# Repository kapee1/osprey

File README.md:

## Remix of the most beautiful ergonomic monosplit in my opinion

### Why did i do it? 
I really likes how does look original Osprey, but it is very difficult to assemble it yourself. This remix allows you to build it much easier and it still can be wireless! However, the assembly is not the easiest due to the size of the diodes.
### What changed? 
It uses SuperMini as controller. I used original PCB as template, so outline barely changed to fit a MSK swtich near USB-port. I have to slightly change case usb-hole and add a switch cutout. But original plate still fits. 
### Thanks
Huge thanks to the [ebastler](https://github.com/ebastler), author of the [original project](https://github.com/ebastler/osprey) for the inspiration and for the great work he did on the original project and [aroum](https://github.com/aroum) for his kind help and advices. 
### BOM
To build firmware, simply clone this repo: https://github.com/kapee1/osprey-remix-zmk-config

| Part    |  Amount   |     |
| --- | --- | --- |
|   Osprey-remix PCB         |  1  |  1.2mm   |
|   Osprey Plate             |  1  |  1.2mm   |
|   Osprey-remix Bottom case |   1  |     |
|   Osprey-remix Top case    |   1  |     |
|   M2 x 8mm screws          |  9   |     |
|   Threaded M2 inserts      |  9   |     |
|   SuperMini or Nice!Nano   |  1   |     |
|   Kailh Choc Hotswap sockets    |  42   |     |
|   1N4148WS SOD-323 Diodes   |  42  |     |
|   MSK-12C01 Switch         |  1   |     |
|   502030 Battery           |  1   |     |
|   Round 8mm feets          |  7   |     |

## Photos

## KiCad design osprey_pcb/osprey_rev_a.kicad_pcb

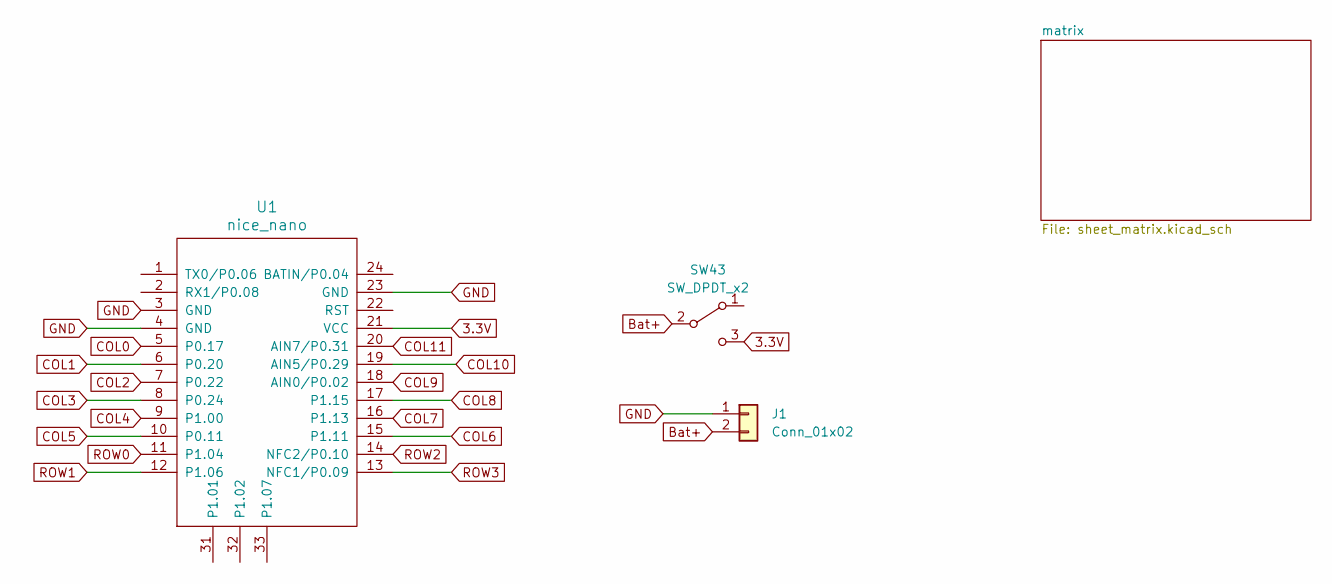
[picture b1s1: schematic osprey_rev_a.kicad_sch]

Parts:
J1: Conn_01x02; JST_ACH_BM02B-ACHSS-GAN-ETF_1x02-1MP_P1.20mm_Vertical
SW43: SW_DPDT_x2; MSK12C02
U1: nice_nano; NiceNano

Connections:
3.3V: SW43.3 (C), U1.21 (VCC), U1.26
Bat+: J1.2, SW43.2 (B); also elsewhere on the board
COL0: U1.5 (P0.17); also elsewhere on the board
COL1: U1.6 (P0.20); also elsewhere on the board
COL2: U1.7 (P0.22); also elsewhere on the board
COL3: U1.8 (P0.24); also elsewhere on the board
COL4: U1.9 (P1.00); also elsewhere on the board
COL5: U1.10 (P0.11); also elsewhere on the board
COL6: U1.15 (P1.11); also elsewhere on the board
COL7: U1.16 (P1.13); also elsewhere on the board
COL8: U1.17 (P1.15); also elsewhere on the board
COL9: U1.18 (AIN0/P0.02); also elsewhere on the board
COL10: U1.19 (AIN5/P0.29); also elsewhere on the board
COL11: U1.20 (AIN7/P0.31); also elsewhere on the board
GND: J1.1, U1.3 (GND), U1.4 (GND), U1.23 (GND), U1.25; also elsewhere on the board
ROW0: U1.11 (P1.04); also elsewhere on the board
ROW1: U1.12 (P1.06); also elsewhere on the board
ROW2: U1.14 (NFC2/P0.10); also elsewhere on the board
ROW3: U1.13 (NFC1/P0.09); also elsewhere on the board

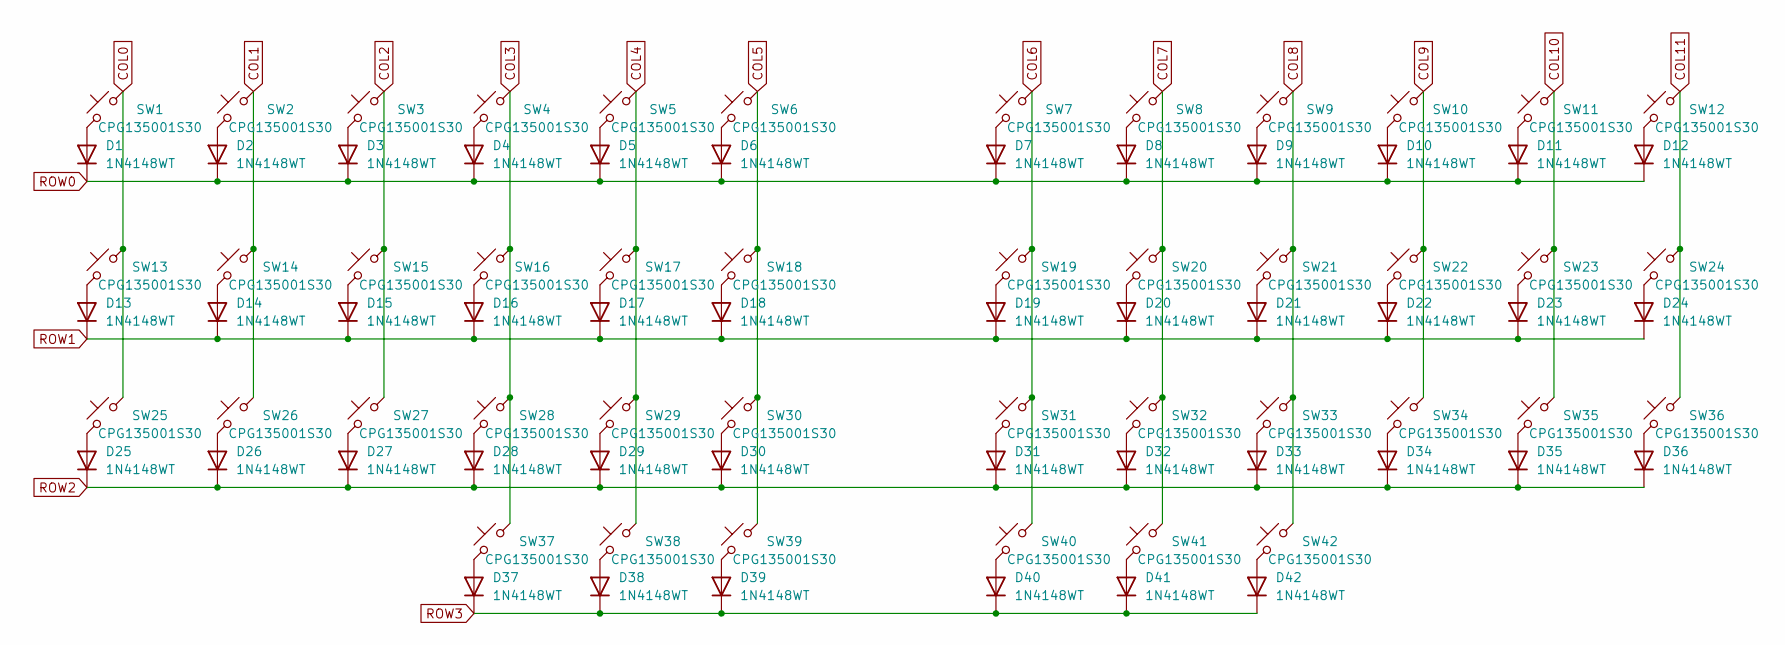
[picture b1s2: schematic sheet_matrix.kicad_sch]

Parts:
D1, D2, D3, D4, D5, D6, D7, D8, D9, D10, D11, D12, D13, D14, D15, D16, D17, D18, D19, D20, D21, D22, D23, D24, D25, D26, D27, D28, D29, D30, D31, D32, D33, D34, D35, D36, D37, D38, D39, D40, D41, D42: 1N4148WT; D_SOD-323_HandSoldering
SW1, SW2, SW3, SW4, SW5, SW6, SW7, SW8, SW9, SW10, SW11, SW12, SW13, SW14, SW15, SW16, SW17, SW18, SW19, SW20, SW21, SW22, SW23, SW24, SW25, SW26, SW27, SW28, SW29, SW30, SW31, SW32, SW33, SW34, SW35, SW36, SW37, SW38, SW41, SW42: CPG135001S30; SW_choc_HS_1u
SW39, SW40: CPG135001S30; SW_choc_HS_1.5u

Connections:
COL0: SW1.1, SW13.1, SW25.1; also elsewhere on the board
COL1: SW2.1, SW14.1, SW26.1; also elsewhere on the board
COL2: SW3.1, SW15.1, SW27.1; also elsewhere on the board
COL3: SW4.1, SW16.1, SW28.1, SW37.1; also elsewhere on the board
COL4: SW5.1, SW17.1, SW29.1, SW38.1; also elsewhere on the board
COL5: SW6.1, SW18.1, SW30.1, SW39.1; also elsewhere on the board
COL6: SW7.1, SW19.1, SW31.1, SW40.1; also elsewhere on the board
COL7: SW8.1, SW20.1, SW32.1, SW41.1; also elsewhere on the board
COL8: SW9.1, SW21.1, SW33.1, SW42.1; also elsewhere on the board
COL9: SW10.1, SW22.1, SW34.1; also elsewhere on the board
COL10: SW11.1, SW23.1, SW35.1; also elsewhere on the board
COL11: SW12.1, SW24.1, SW36.1; also elsewhere on the board
unnamed: D1.2 (A), SW1.2
unnamed: D2.2 (A), SW2.2
unnamed: D3.2 (A), SW3.2
unnamed: D4.2 (A), SW4.2
unnamed: D5.2 (A), SW5.2
unnamed: D6.2 (A), SW6.2
unnamed: D7.2 (A), SW7.2
unnamed: D8.2 (A), SW8.2
unnamed: D9.2 (A), SW9.2
unnamed: D10.2 (A), SW10.2
unnamed: D11.2 (A), SW11.2
unnamed: D12.2 (A), SW12.2
unnamed: D13.2 (A), SW13.2
unnamed: D14.2 (A), SW14.2
unnamed: D15.2 (A), SW15.2
unnamed: D16.2 (A), SW16.2
unnamed: D17.2 (A), SW17.2
unnamed: D18.2 (A), SW18.2
unnamed: D19.2 (A), SW19.2
unnamed: D20.2 (A), SW20.2
unnamed: D21.2 (A), SW21.2
unnamed: D22.2 (A), SW22.2
unnamed: D23.2 (A), SW23.2
unnamed: D24.2 (A), SW24.2
unnamed: D25.2 (A), SW25.2
unnamed: D26.2 (A), SW26.2
unnamed: D27.2 (A), SW27.2
unnamed: D28.2 (A), SW28.2
unnamed: D29.2 (A), SW29.2
unnamed: D30.2 (A), SW30.2
unnamed: D31.2 (A), SW31.2
unnamed: D32.2 (A), SW32.2
unnamed: D33.2 (A), SW33.2
unnamed: D34.2 (A), SW34.2
unnamed: D35.2 (A), SW35.2
unnamed: D36.2 (A), SW36.2
unnamed: D37.2 (A), SW37.2
unnamed: D38.2 (A), SW38.2
unnamed: D39.2 (A), SW39.2
unnamed: D40.2 (A), SW40.2
unnamed: D41.2 (A), SW41.2
unnamed: D42.2 (A), SW42.2
ROW0: D1.1 (K), D2.1 (K), D3.1 (K), D4.1 (K), D5.1 (K), D6.1 (K), D7.1 (K), D8.1 (K), D9.1 (K), D10.1 (K), D11.1 (K), D12.1 (K); also elsewhere on the board
ROW1: D13.1 (K), D14.1 (K), D15.1 (K), D16.1 (K), D17.1 (K), D18.1 (K), D19.1 (K), D20.1 (K), D21.1 (K), D22.1 (K), D23.1 (K), D24.1 (K); also elsewhere on the board
ROW2: D25.1 (K), D26.1 (K), D27.1 (K), D28.1 (K), D29.1 (K), D30.1 (K), D31.1 (K), D32.1 (K), D33.1 (K), D34.1 (K), D35.1 (K), D36.1 (K); also elsewhere on the board
ROW3: D37.1 (K), D38.1 (K), D39.1 (K), D40.1 (K), D41.1 (K), D42.1 (K); also elsewhere on the board

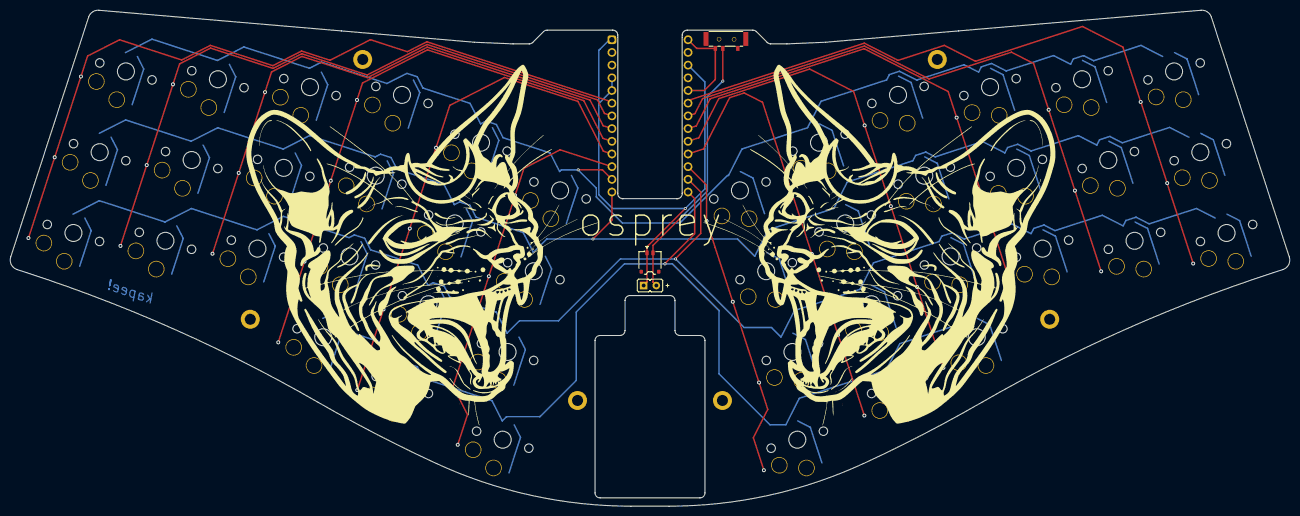
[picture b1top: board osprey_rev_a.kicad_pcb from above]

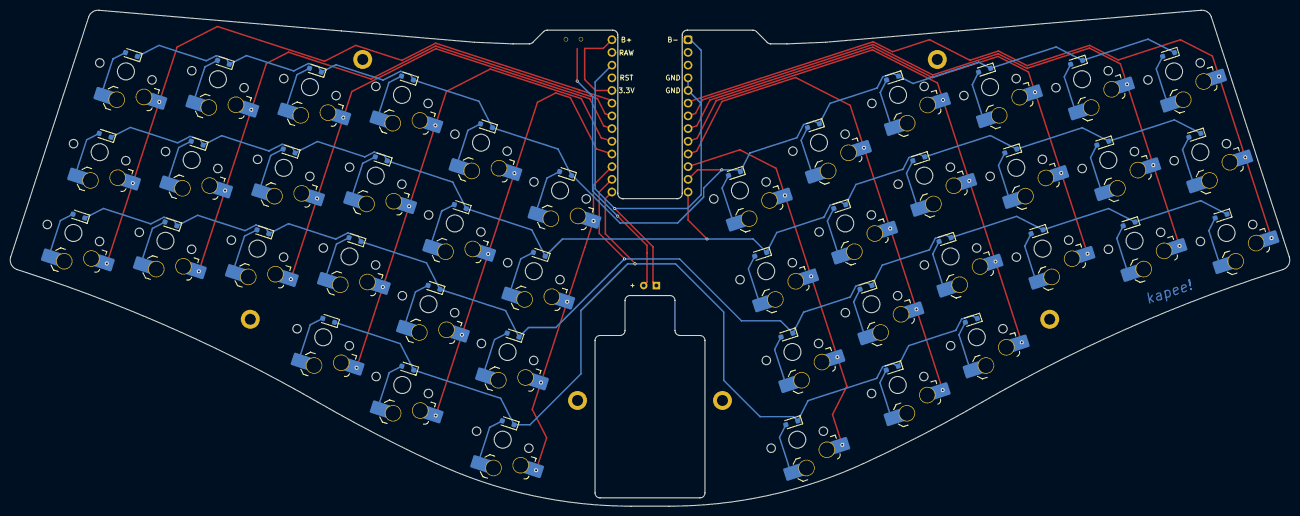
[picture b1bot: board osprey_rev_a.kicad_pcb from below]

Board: 2 copper layers, 256.1 x 99.3 mm, 94 parts (88 on the bottom side), 61 nets.

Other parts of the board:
H1, H2, H3, H4, H5, H6: M2; MountingHole_2.2mm_M2_DIN965_Pad
J3: Conn_01x02_Male; PinHeader_1x2_P2.54mm_Vertical

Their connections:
Bat+: J3.2; also elsewhere on the board
GND: J3.1; also elsewhere on the board

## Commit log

2024-05-16 release v1
2024-05-24 updated firmware
